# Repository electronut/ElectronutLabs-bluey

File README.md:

## What is Bluey?

**Bluey** is an Open Source BLE (Bluetooth Low Energy) development board with Temperature, Humidity, Ambient Light and
Accelerometer sensors.

Bluey uses the Nordic nRF52832 BLE
SoC (System on a Chip) which has an ARM Cortex-M4F CPU and a 2.4 GHz radio
that supports BLE and other proprietary wireless protocols. It also supports
NFC, and in fact the board comes with a built-in NFC PCB antenna.

### Specifications

- Nordic nRF52832 QFAA BLE SoC (512k Flash/ 64k RAM)
- TI HDC1010 Temperature/Humidity sensor
- APDS-9300-020 ambient light sensor
- ST Micro LSM6DS3 accelerometer
- CREE RGB LED
- CP2104 USB interface
- 2 push buttons
- Coin cell holder
- Micro SD slot
- 2.4 GHz PCB antenna
- NFC PCB antenna

## Getting Started with Bluey

Bluey is shipped with either Arduino bootloader or Nordic DFU-OTA bootloader as per the selection at the time of purchase. While Arduino bootloader facilitates programming Bluey using Arduino IDE via serial USB cable, Nordic's DFU-OTA bootloader allows the user to update device firmware using Nordic's software development kit (SDK) and nRF Connect mobile application over bluetooth.

We have created an [Arduino library](https://github.com/electronut/ElectronutLabs_Bluey_Arduino_Library) with example projects to help you get started quickly.

<h3><a href="#Arduino">Guide: Using Arduino</a></h3>

<h3><a href="#Nordic OTA">Guide: Using Nordic SDK</a></h3>

<hr>

<h2 id="Arduino"> Guide: Using Arduino </h2>

## Installation

Uploading without programmer requires bootloader programmed on the board. The repo [electronut/bluey_serial_dfu_bootloader](https://github.com/electronut/bluey_serial_dfu_bootloader/) 
contains the source and precompiled hex file of the bootloader as `hex/s132_nrf52_2.0.0_softdevice.hex`.

The bootloader has the softdevice s132 in it, so no other action is needed to use the BLE Peripheral library.

Bootloader mode is triggered by pressing and holding both prss buttons on bluey and releasing the reset button. The blue LED will start blinkng at an accelerating rate repeatedly to indicate that the bootloader mode is active.

### Board Manager

 1. [Download and install the Arduino IDE](https://www.arduino.cc/en/Main/Software) (At least v1.6.12)
 2. Start the Arduino IDE
 3. Go into Preferences
 4. Add ```https://raw.githubusercontent.com/electronut/arduino-boards/master/package_electronutlabs_boards_index.json``` as an "Additional Board Manager URL"
 5. Open the Boards Manager from the Tools -> Board menu and install "Electronut labs nRF5 Boards"
 6. Select 'Electronut labs bluey' from the Tools -> Board menu

__NOTE:__ During installation it takes the Arduino IDE a few minutes to extract the tools after they have been downloaded, please be patient.

## Uploading Bootloader

Although Bluey is shipped with the bootloader that enables programming the device using Arduino IDE, in case you erase the bootloader from Bluey, it is possible to flash it again using a [Bumpy](http://electronut.in/portfolio/bumpy/).

### Steps

1. Download [bootloader](https://github.com/electronut/bluey_serial_dfu_bootloader/)
2. Open command prompt and access the directory containing bootloader hex file.
3. Follow steps as mentioned in the Bumpy [github](https://github.com/electronut/ElectronutLabs-bumpy) repository to connect and attach to Bluey target.
4. Issue: `load s132_nrf52_2.0.0_softdevice.hex` command. Wait for the command to execute and load the file completely.
5. Issue: `detach` command to free the target.
6. Issue: `Quit` command to close arm-gdb debugger.
7. Unplug Bumpy.
8. Connect Bluey to your PC via USB cable. You should notice the familiar blue LED blinkking at an accelerating rate, indicating Bluey is in bootloader mode.

## Usage

* After tools installation, you can now select "Electronut labs bluey" from the tools menu, and other related options. 

* Bluey comes preprogrammed with [serial DFU bootloader](https://github.com/electronut/bluey_serial_dfu_bootloader/), which Nordic's nrfjprog utility can program using serial connection. To trigger bootloader, press and hold button1, press the Reset button and then release button1.

* Bluey's blue LED will start blinking in a 'timebomb' pattern, indicating that it is in DFU bootloader mode. Now you can press upload button in arduino IDE to program your code.

* Bluey library for arduino is available at [ElectronutLabs_Bluey_Arduino_Library](https://github.com/electronut/ElectronutLabs_Bluey_Arduino_Library) repository. Download the zip file from github repository and extract the files to *Documents/Arduino/libraries* directory for Windows OS.

### Steps

* Set the device in bootloader mode. To trigger bootloader, press and hold button1 (SW3) , press the Reset button (RST) and then release button1.

* Go to: Tools > Boards. Select **Electronut labs Bluey**.

* Go to: Tools > Softdevice. Select **S132**.

* Ensure Low Frequency Clock is set to **Crystal Oscillator** under Tools menu.

* Select appropriate COM Port assigned to Bluey.

* Click on **Upload** under Sketch menu or use **Ctrl + U** combination to upload code to Bluey.

* Once code is upload, perform a manual reset by pressing **RST** button once.

## Pin mapping

```
                    Connector P3 on bluey

     A0       P0.02/AIN0   | 1   2 | P0.26        D0
     A1       P0.03/AIN1   | 3   4 | P0.27        D1
     A2       P0.04/AIN2   | 5   6 | P0.24/AIN4   A3
     D2            P0.22   | 7   8 | P0.29/AIN5   A4
     D3            P0.23   | 9  10 | P0.30/AIN6   A5
     D4            P0.24   | 11 12 | P0.31/AIN7   A6
     D5            P0.25   | 13 14 | Ex_vin
                     GND   | 15 16 | 3v3
                     GND   | 17 18 | GND

          button D6  - P0.16
              R  D7  - P0.19
              G  D8  - P0.18
              B  D9  - P0.17

      D10     SCL - P0.11    DRDYn - P0.12   D11
      D12     SDA - P0.13      INT - P0.14   D13
      D14    INT1 - P0.15     INT2 - P0.20   D15

              RXD - P0.08    TXD - P0.06
              RTS - P0.05    CTS - P0.07

              SS - P0.22    SCK - P0.25
            MISO - P0.24   MOSI - P0.23
```

* LED and button pins can be referenced by `PIN_LEDR`, `PIN_LEDG`, `PIN_LEDB` ,`LED_BUILTIN` (red one), `PIN_BUTTON` in arduino code.

## Low Frequency Clock Source (LFCLKSRC)

Bluey has an external 32 kHz crystal connected, thus, it will be used as the source for the low frequency clock. The internal 32 kHz RC oscillator can be used by removing the external crystal. The low frequency clock is used by the `delay(ms)` and `millis()` Arduino API's.

Bluey has an additional menu item under `Tools -> Low Frequency Clock` that allows you to select the low frequency clock source.

## BLEPeriphial Arduino Library

* [arduino-BLEPeripheral](https://github.com/sandeepmistry/arduino-BLEPeripheral) library can be used creating BLE applications with bluey. Follow installation steps on it's `README`. See the library's [API](https://github.com/sandeepmistry/arduino-BLEPeripheral/blob/master/API.md) for more details on usage.

* Ensure that Softdevice:"S132" is selected under tools menu. This is essential to compile BLE examples.

* _NOTE_: Although the description says "nRF8001 or nRF51822", but nRF52832 is also supported because despite changes in CPU and peripherals, the radio interface is identical in both (API is same, but there might be changes in power/sensitivity etc.)

* Once installed, you can see examples for this in examples menu. You can run most examples without modifications, unless some specify LED or button pins different from bluey's, in which case, just replace pin numbers with `LED_BUILTIN`, or `PIN_BUTTON` etc.

* Use [nRF connect](https://play.google.com/store/apps/details?id=no.nordicsemi.android.mcp&hl=en) (and other apps from nordic on play store) to scan, connect, interact with BLE peripherals created with these examples.

<hr />

<h2 id="Nordic OTA"> Guide: Using Nordic SDK </h2>

To get a project up and running with **bluey**, you need to first build the code to generate a *.hex*
file and then upload it to the board.

### Building code for Bluey

If you are just getting started with the nRF52832, we recommend that you set up and
use the Nordic nRF5 SDK for programming **bluey**. [Click here](nrf5-sdk-setup.md) to
read our *Getting Started with nRF5 SDK* guide.

### Uploading code to Bluey

There are two main ways of uploading code into **bluey**:

1. Use the built-in OTA (over the air) bootloader which lets you upload code
using a phone. [Click here](ota-prog.md) to read about this option.

2. A much more powerful option is to use an external programmer that can both
upload and debug your code. Here are a few ways of doing this:
   1. Use our inexpensive *Black Magic Probe* compatible [Bumpy SWD programmer][1]
   which was designed exactly for this purpose.
   2. Using a cheap programmer loaded with *Black Magic Probe* firmware. [Click here](blackmagic-prog.md) to learn about this option.
   3. Using the Nordic nRF52-DK. [Click here](nRF52-DK-prog.md) to explore this option.

### Powering Bluey

You can power **bluey** in several ways:

1. Using the 5V micro USB connector (which also gives you the
  option to print debug messages via UART).
2. The + / -  power supply pins which can take regular 2.54 mm header pins,
a JST connector for a 3.7 V LiPo battery, or a 3.5 mm terminal block.
3. A CR2032 coin cell for low power applications.

The sensors on bluey require a minimum of 2.7 Volts to function properly.
Please note that the *maximum power supply to bluey is 6 Volts*. Do not
exceed it! We also have reverse polarity protection on all power supplies,
but better not to tempt fate. :-)

<hr />

## What can you do with Bluey?

You can use **bluey** for a wide range of projects. The BLE part is ideal for IoT
projects, or if you want to control something with your phone. The nRF52832 SoC
has a powerful ARM Cortex-M4F CPU, so you can use this board for general purpose
microcontroller projects as well.

With BLE and useful built-in sensors, **bluey** is a great platform for learning
IoT, BLE programming, ARM, and microcontrollers in general. In fact, it's being
currently used in Embedded Systems training courses.

The [code](code/) folder
in this repository has a bunch of interesting demo projects that we have built using
**bluey** - so do take a look!

[1]: https://www.tindie.com/stores/ElectronutLabs/

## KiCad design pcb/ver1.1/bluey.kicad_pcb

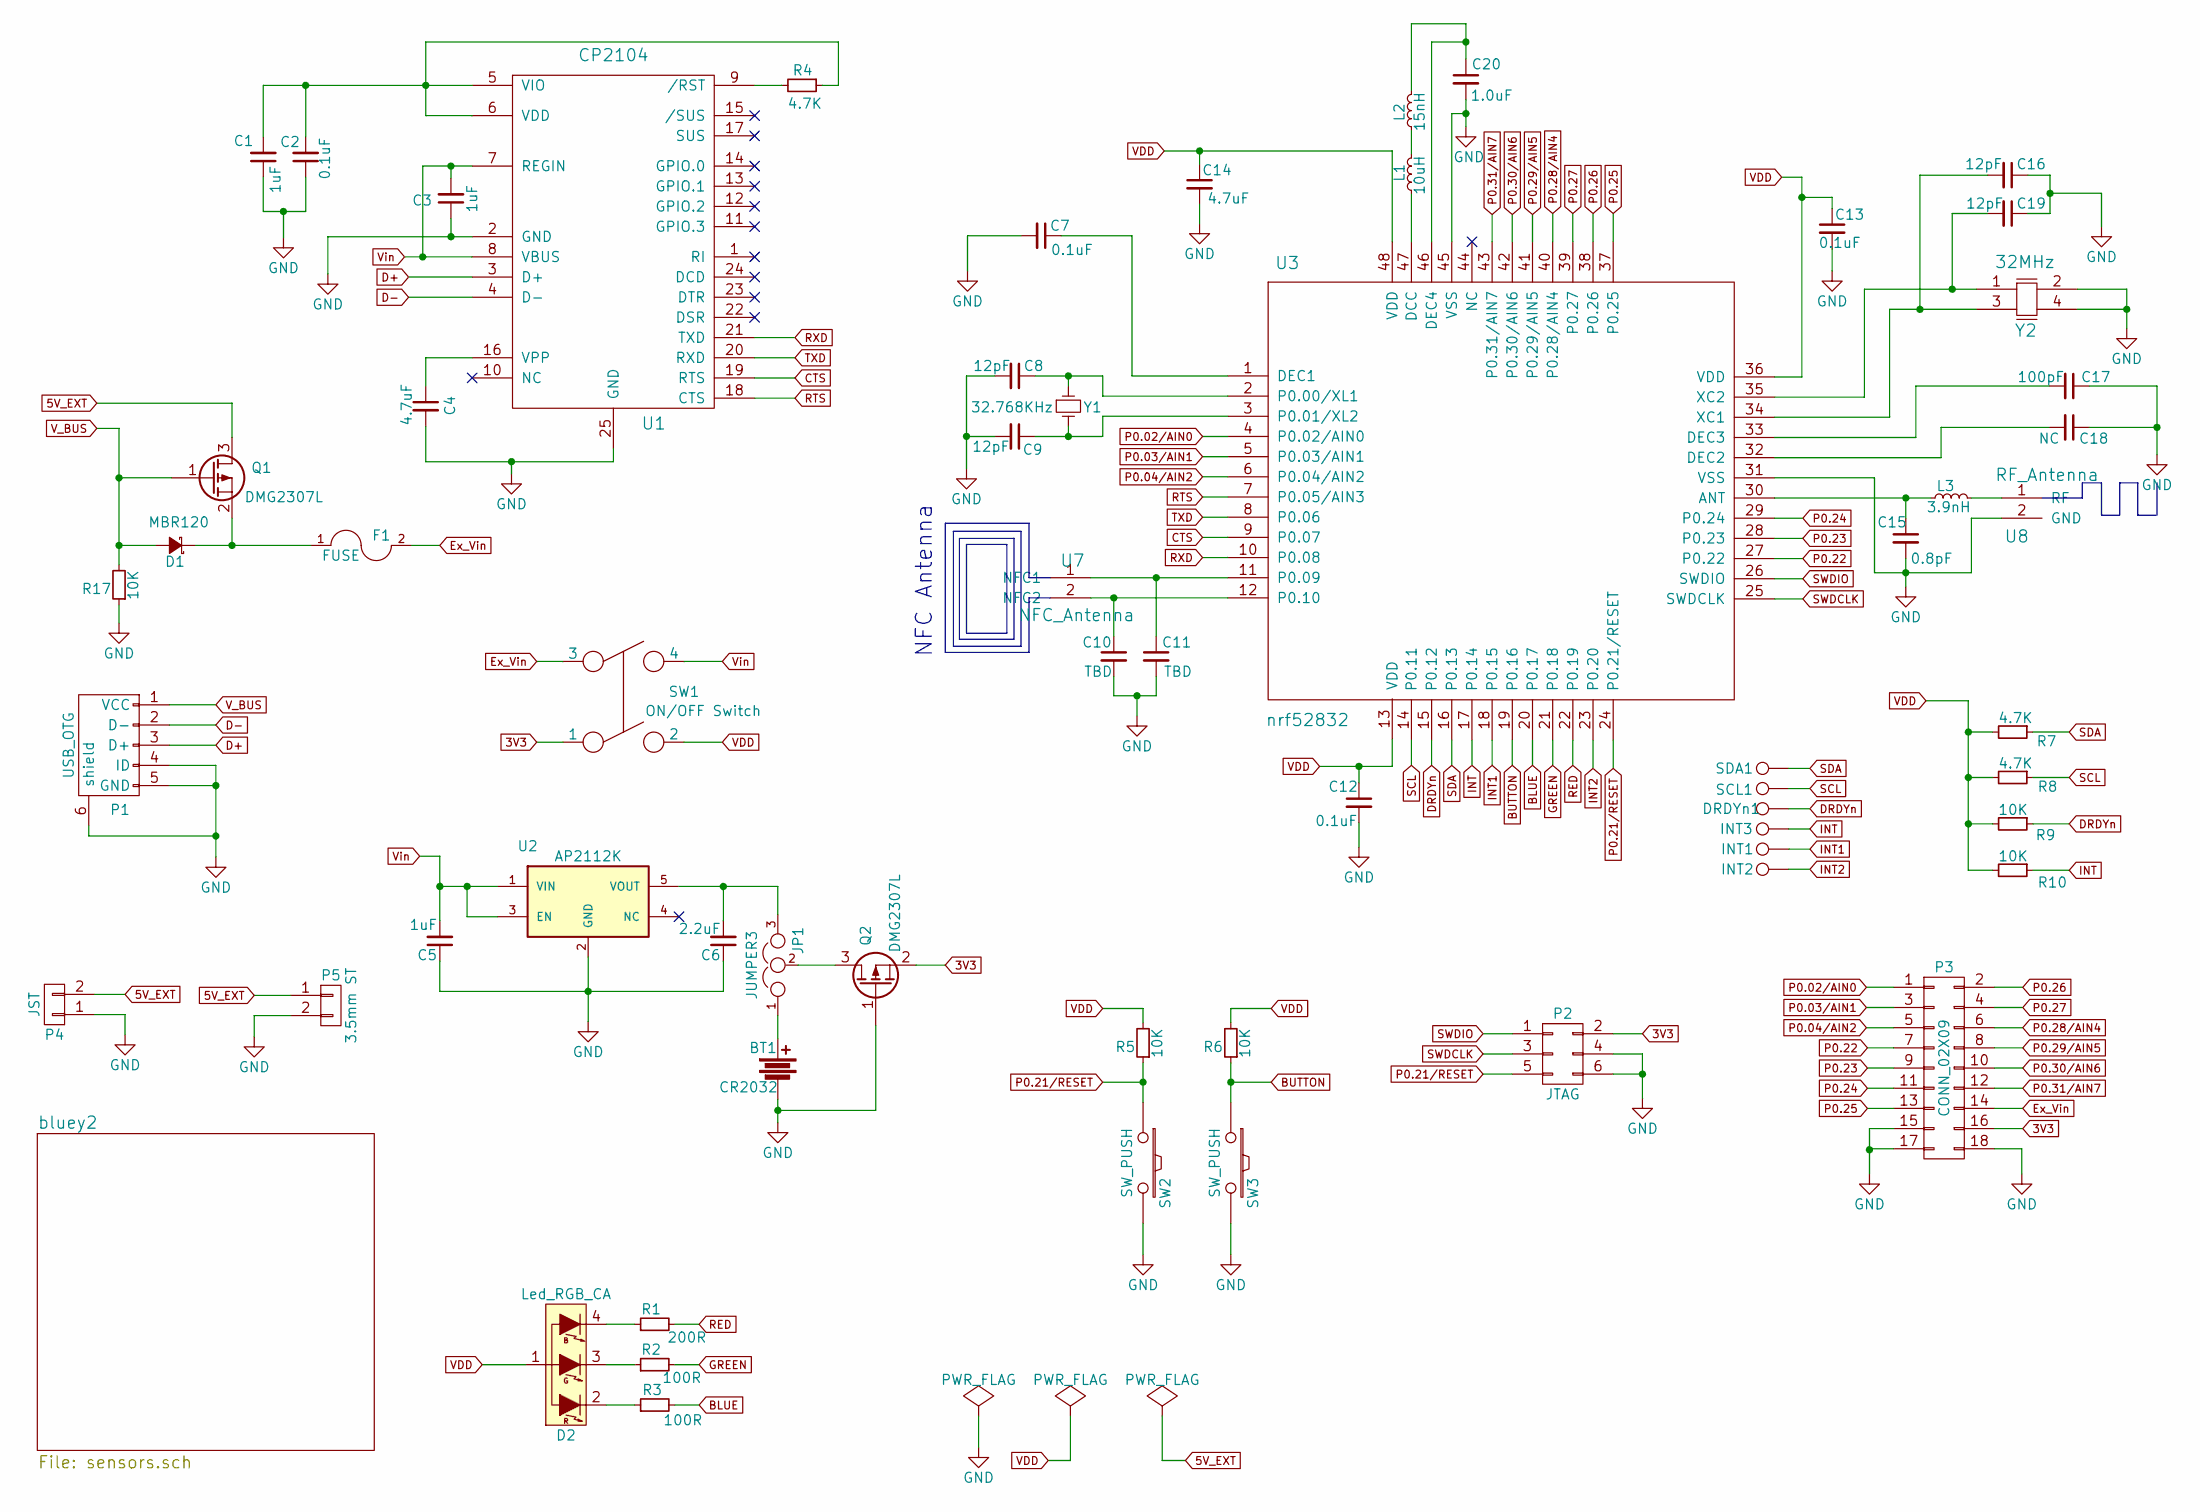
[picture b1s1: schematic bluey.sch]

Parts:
BT1: CR2032; BT2032
C1, C3, C5: 1uF; C_0603
C2: 0.1uF; C_0603
C4, C14: 4.7uF; C_0603
C6: 2.2uF; C_0603
C7, C12, C13: 0.1uF; C_0402
C8, C9, C16, C19: 12pF; C_0402
C10, C11: TBD; C_0402
C15: 0.8pF; C_0402
C17: 100pF; C_0402
C18: NC; C_0402
C20: 1.0uF; C_0603
D1: MBR120; S.Diode
D2: Led_RGB_CA; CREE-CA
DRDYn1: TEST_1P; TP
F1: FUSE; Fuse_PTC
INT1, INT2, INT3: TEST_1P; TP
JP1: JUMPER3; Pin_Header_Straight_1x03_Pitch2.54mm
L1: 10uH; Neosid_Inductor_SM0603CG
L2: 15nH; L_0402
L3: 3.9nH; L_0402
P1: USB_OTG; Micro_USB_5.9mm
P2: JTAG; Pin_Header_Straight_2x03_Pitch2.54mm
P3: CONN_02X09; Pin_Header_Straight_2x09_Pitch2.54mm
P4: JST; JST-2-PTH
P5: 3.5mm ST; TerminalBlock_Pheonix_PT-3.5mm_2pol
Q1, Q2: DMG2307L; SOT-23
R1: 200R; R_0603
R2, R3: 100R; R_0603
R4, R7, R8: 4.7K; R_0603
R5, R6, R9, R10, R17: 10K; R_0603
SCL1: TEST_1P; TP
SDA1: TEST_1P; TP
SW1: ON/OFF Switch; tactile_switch
SW2, SW3: SW_PUSH; peter-switch
U1: CP2104; CP2104_QFN-24_4x4mm
U2: AP2112K; SOT-23-5
U3: nrf52832
U7: NFC_Antenna; nfc
U8: RF_Antenna; Antenna-2.45GHZ_mirror
Y1: 32.768KHz; ABS07_crystal
Y2: 32MHz; 32MHz_crystal

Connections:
3V3: P2.2, P3.16, Q2.2 (S), SW1.1
5V_EXT: P4.2, P5.1, Q1.3 (D)
BLUE: R3.2, U3.20 (P0.17)
BUTTON: R6.1, SW3.1, U3.19 (P0.16)
CTS: U1.19 (RTS), U3.9 (P0.07)
D+: P1.3 (D+), U1.3 (D+)
D-: P1.2 (D-), U1.4 (D-)
DRDYn: DRDYn1.1, R9.1, U3.15 (P0.12); also elsewhere on the board
Ex_Vin: F1.2, P3.14, SW1.3
GND: BT1.2, C1.1, C2.1, C3.1, C4.2, C5.1, C6.1, C7.2, C8.2, C9.2, C10.2, C11.2, C12.2, C13.2, C14.2, C15.2, C16.1, C17.1, C18.1, C19.1, C20.2, P1.4 (ID), P1.5 (GND), P1.6 (shield), P2.4, P2.6, P3.15, P3.17, P3.18, P4.1, P5.2, Q2.1 (G), R17.1, SW2.2, SW3.2, U1.2 (GND), U1.25 (GND), U2.2 (GND), U3.31 (VSS), U3.45 (VSS), U8.2 (GND), Y2.2, Y2.4; also elsewhere on the board
GREEN: R2.2, U3.21 (P0.18)
INT: INT3.1, R10.1, U3.17 (P0.14); also elsewhere on the board
INT1: INT1.1, U3.18 (P0.15); also elsewhere on the board
INT2: INT2.1, U3.23 (P0.20); also elsewhere on the board
unnamed: BT1.1, JP1.1
unnamed: C1.2, C2.2, R4.1, U1.5 (VIO), U1.6 (VDD)
unnamed: C4.1, U1.16 (VPP)
unnamed: C6.2, JP1.3, U2.5 (VOUT)
unnamed: C7.1, U3.1 (DEC1)
unnamed: C8.1, U3.2 (P0.00/XL1), Y1.1
unnamed: C9.1, U3.3 (P0.01/XL2), Y1.2
unnamed: C10.1, U3.12 (P0.10), U7.2 (NFC2)
unnamed: C11.1, U3.11 (P0.09), U7.1 (NFC1)
unnamed: C15.1, L3.1, U3.30 (ANT)
unnamed: C16.2, U3.34 (XC1), Y2.3
unnamed: C17.2, U3.33 (DEC3)
unnamed: C18.2, U3.32 (DEC2)
unnamed: C19.2, U3.35 (XC2), Y2.1
unnamed: C20.1, L2.2, U3.46 (DEC4)
unnamed: D1.1 (K), F1.1, Q1.2 (S)
unnamed: D2.2 (R), R3.1
unnamed: D2.3 (G), R2.1
unnamed: D2.4 (B), R1.1
unnamed: JP1.2, Q2.3 (D)
unnamed: L1.1, U3.47 (DCC)
unnamed: L1.2, L2.1
unnamed: L3.2, U8.1 (RF)
unnamed: R4.2, U1.9 (/RST)
P0.02/AIN0: P3.1, U3.4 (P0.02/AIN0)
P0.03/AIN1: P3.3, U3.5 (P0.03/AIN1)
P0.04/AIN2: P3.5, U3.6 (P0.04/AIN2)
P0.21/RESET: P2.5, R5.1, SW2.1, U3.24 (P0.21/RESET)
P0.22: P3.7, U3.27 (P0.22); also elsewhere on the board
P0.23: P3.9, U3.28 (P0.23); also elsewhere on the board
P0.24: P3.11, U3.29 (P0.24); also elsewhere on the board
P0.25: P3.13, U3.37 (P0.25); also elsewhere on the board
P0.26: P3.2, U3.38 (P0.26)
P0.27: P3.4, U3.39 (P0.27)
P0.28/AIN4: P3.6, U3.40 (P0.28/AIN4)
P0.29/AIN5: P3.8, U3.41 (P0.29/AIN5)
P0.30/AIN6: P3.10, U3.42 (P0.30/AIN6)
P0.31/AIN7: P3.12, U3.43 (P0.31/AIN7)
RED: R1.2, U3.22 (P0.19)
RTS: U1.18 (CTS), U3.7 (P0.05/AIN3)
RXD: U1.21 (TXD), U3.10 (P0.08)
SCL: R8.1, SCL1.1, U3.14 (P0.11); also elsewhere on the board
SDA: R7.1, SDA1.1, U3.16 (P0.13); also elsewhere on the board
SWDCLK: P2.3, U3.25 (SWDCLK)
SWDIO: P2.1, U3.26 (SWDIO)
TXD: U1.20 (RXD), U3.8 (P0.06)
VDD: C12.1, C13.1, C14.1, D2.1, R5.2, R6.2, R7.2, R8.2, R9.2, R10.2, SW1.2, U3.13 (VDD), U3.36 (VDD), U3.48 (VDD); also elsewhere on the board
V_BUS: D1.2 (A), P1.1 (VCC), Q1.1 (G), R17.2
Vin: C3.2, C5.2, SW1.4, U1.7 (REGIN), U1.8 (VBUS), U2.1 (VIN), U2.3 (EN)

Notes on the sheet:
NFC Antenna

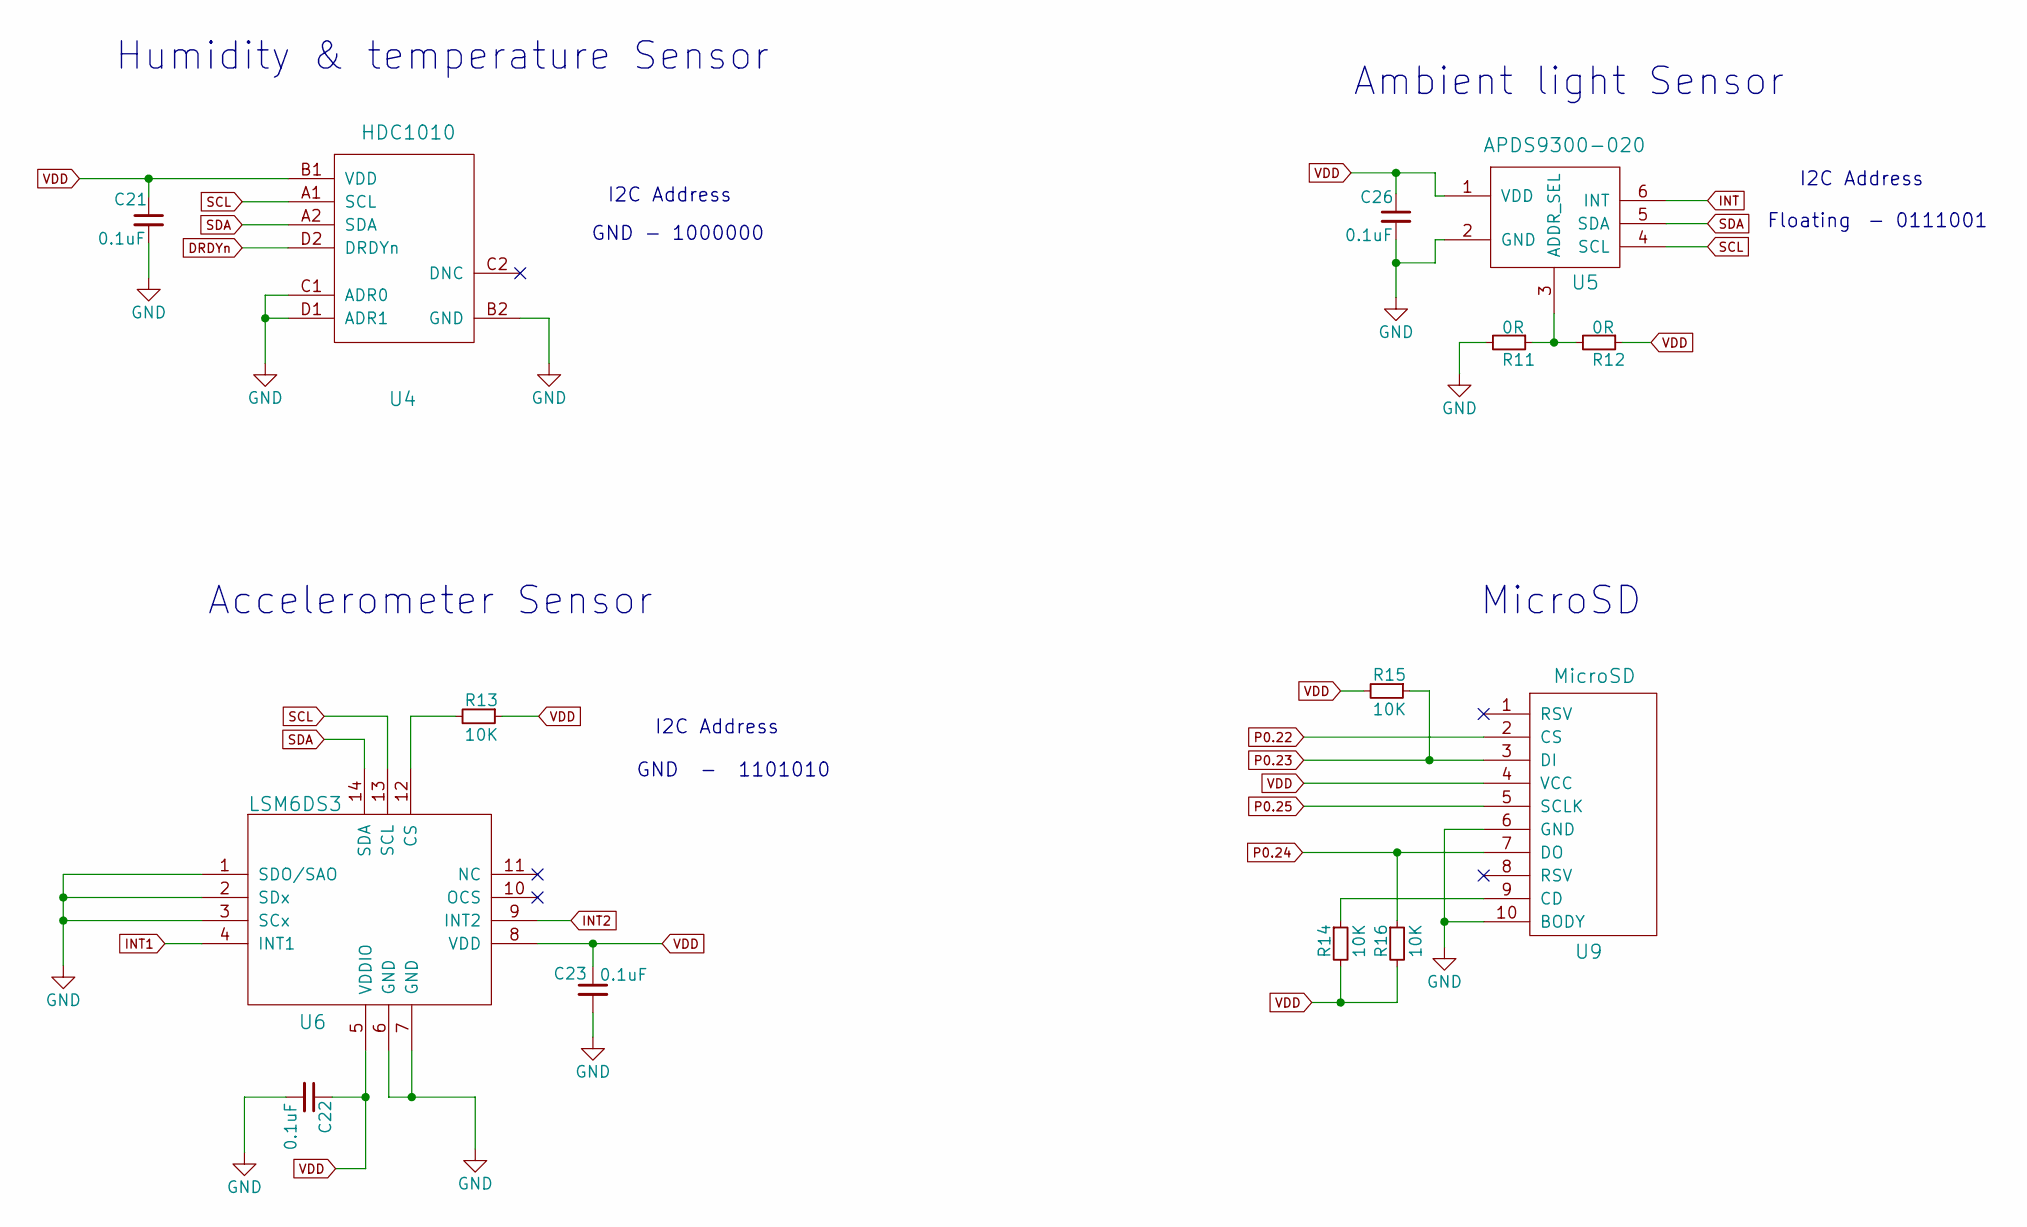
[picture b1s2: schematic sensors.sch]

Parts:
C21, C22, C23, C26: 0.1uF; C_0603
R11, R12: 0R; R_0603
R13, R14, R15, R16: 10K; R_0603
U4: HDC1010
U5: APDS9300-020; APDS9301
U6: LSM6DS3
U9: MicroSD; MicroSD_CardHolder

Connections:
DRDYn: U4.D2 (DRDYn); also elsewhere on the board
GND: C21.2, C22.2, C23.2, C26.2, R11.2, U4.B2 (GND), U4.C1 (ADR0), U4.D1 (ADR1), U5.2 (GND), U6.1 (SDO/SAO), U6.2 (SDx), U6.3 (SCx), U6.6 (GND), U6.7 (GND), U9.6 (GND), U9.10 (BODY); also elsewhere on the board
INT: U5.6 (INT); also elsewhere on the board
INT1: U6.4 (INT1); also elsewhere on the board
INT2: U6.9 (INT2); also elsewhere on the board
unnamed: R11.1, R12.2, U5.3 (ADDR_SEL)
unnamed: R13.2, U6.12 (CS)
unnamed: R14.1, U9.9 (CD)
P0.22: U9.2 (CS); also elsewhere on the board
P0.23: R15.1, U9.3 (DI); also elsewhere on the board
P0.24: R16.1, U9.7 (DO); also elsewhere on the board
P0.25: U9.5 (SCLK); also elsewhere on the board
SCL: U4.A1 (SCL), U5.4 (SCL), U6.13 (SCL); also elsewhere on the board
SDA: U4.A2 (SDA), U5.5 (SDA), U6.14 (SDA); also elsewhere on the board
VDD: C21.1, C22.1, C23.1, C26.1, R12.1, R13.1, R14.2, R15.2, R16.2, U4.B1 (VDD), U5.1 (VDD), U6.5 (VDDIO), U6.8 (VDD), U9.4 (VCC); also elsewhere on the board

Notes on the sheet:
Humidity & temperature Sensor
Ambient light Sensor
Accelerometer Sensor
MicroSD
I2C Address
GND - 1000000
Floating
- 0111001
GND - 1101010

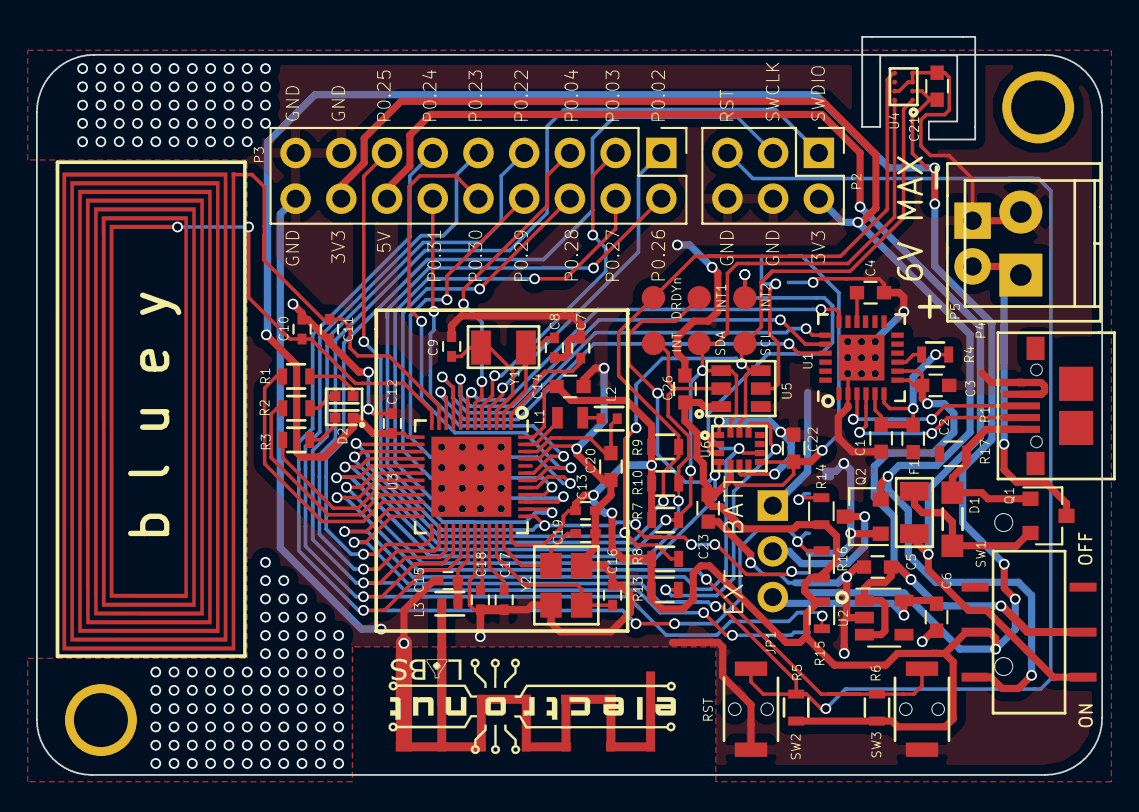
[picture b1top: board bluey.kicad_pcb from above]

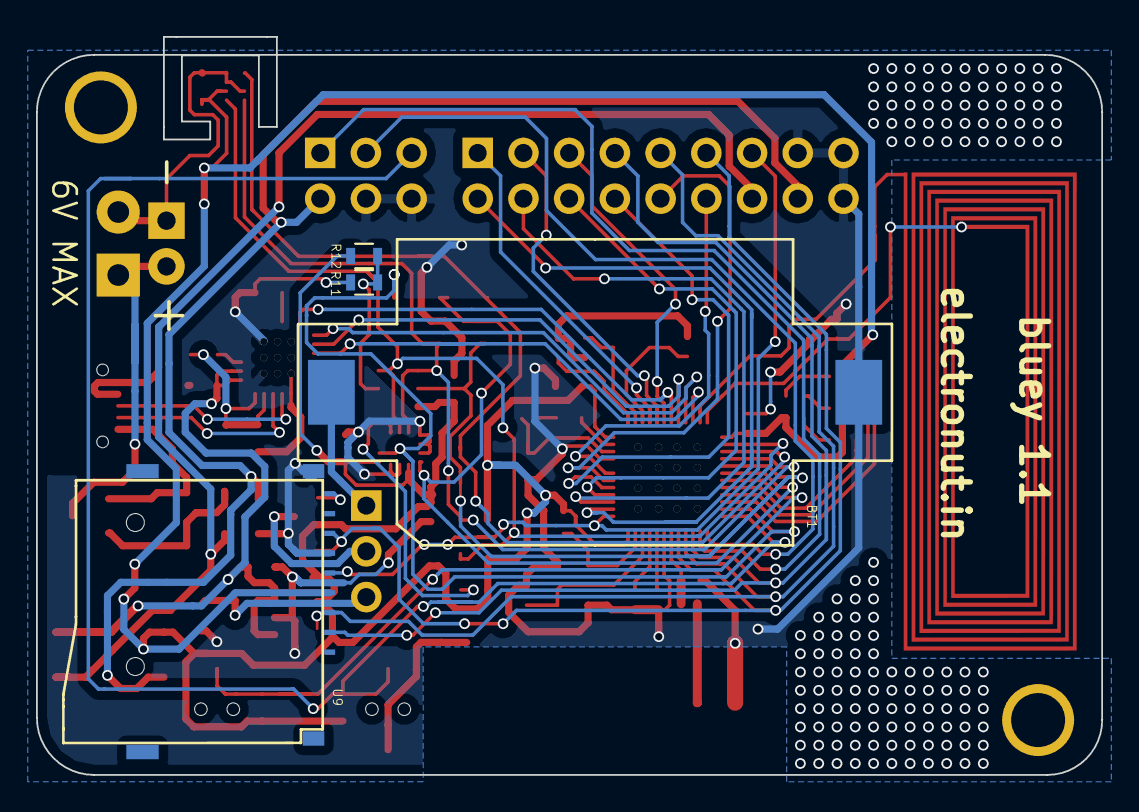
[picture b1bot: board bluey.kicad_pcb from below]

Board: 2 copper layers, 59.2 x 41.0 mm, 76 parts (4 on the bottom side), 66 nets.

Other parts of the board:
DRDYn: TEST_1P; TP
INT: TEST_1P; TP
SCL: TEST_1P; TP
SDA: TEST_1P; TP

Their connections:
DRDYn: DRDYn.1; also elsewhere on the board
INT: INT.1; also elsewhere on the board
SCL: SCL.1; also elsewhere on the board
SDA: SDA.1; also elsewhere on the board

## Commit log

2017-02-23 initial
2017-02-23 added schematic
2017-04-24 added code
2017-05-03 updated examples
2017-05-04 updating readme
2017-05-04 updating docs
2017-05-08 adding readme
2017-05-08 updating beacon project
2017-05-09 added gitignore
2017-05-09 updating license
2017-05-11 sd-card multiple write fix
2017-05-30 private.key file added
2017-05-31 bluey-sensor-test dfu package added
2017-05-31 nfc sensor data update issue fixed
2017-06-01 bluey_ST dfu package added
2017-06-01 added pcb files
2017-06-01 gyroscope errors fixed
2017-06-01 gyroscope update
2017-06-01 bluey-sensor-test images added
2017-06-01 bluey-sensor-test images addeIMU header file edited
2017-06-04 updating beacon readme
2017-06-06 fixed readme
2017-06-16 Custom service example complete
2017-06-16 Custom service Readme added
2017-06-16 Readme updated
2017-07-06 updated bot info
2017-07-18 document arduino support.
2017-07-21 add custom board manager json
2017-07-21 fix json error
2017-07-22 Update installation instructions.
2017-07-26 Update URLs
2017-07-26 Copy install instructions from arduino-bluey repo
2017-07-26 MeArm complete
2017-07-26 screenshots added
2017-07-27 Update which programmer(bumpy) is used when programming bootloader.
2017-07-28 claw issue resolved
2017-07-28 claw event switched
2017-07-30 updated nrf51 doc
2017-08-11 updated with oled
2017-08-18 added WS2812 I2S example
2017-10-31 arduino example added
2017-11-01 restructured
2017-11-01 arduino-ide image added
2018-12-11 Fix html tags
2018-12-19 Fix link
2018-12-20 Fix dead links
2019-02-04 Remove purchase link.
2019-05-16 FIx broken link
2019-06-26 change json URL
